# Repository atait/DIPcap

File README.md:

# DIPcap

A variable capacitor bank built from DIP switches. Six decades of coverage (1 nF to 1 mF) for under $10 to build.

[Explore the files on KiCanvas](https://kicanvas.org/?repo=https%3A%2F%2Fgithub.com%2Fatait%2FDIPcap%2Ftree%2Fmain%2Fdipcap-src)

## What it is

DIPcap covers six decades with 24 switches arranged in three groups of eight, using a non-standard but deliberate value series that guarantees full range coverage with the optimal number of switches per decade.

The calibration guarantee is the interesting part: even with ±10% tolerance on individual capacitors, some combination of switches will converge on any target value.

## Specifications

| Parameter | Value |
|---|---|
| Range | 1 nF – 1,130 µF |
| Max voltage | 0-35V, or ±50V for values < 1 µF |
| Tolerance (dead reckoning) | ±10% |
| Parasitic capacitance (all off) | 28 pF (measured) |
| Output connector | BNC + screw terminal + pin header |
| Cost to build | ~$10/unit (panelized at 8) |

## Why these switch values?

The values per decade are **10, 18, 33, 56** (in units of the decade's base, e.g. ×100pF, ×1nF, etc.). This is not a standard E-series but is drawn from E12 so that common components are available.

Full coverage means every value between 10–100 (in normalized units) is reachable within ±10% by some switch combination, and the next lower decade handles the remaining gap.

The choice of four switches per decade follows from a coverage argument:

- 2³ = 8 steps per decade — not enough; the gap between steps (100÷8 = 12.5) exceeds the range of the next lower decade group (0–10)
- 2⁴ = 16 steps per decade — sufficient; four is the minimum power-of-2 count that guarantees full coverage

## Instructions

There are two ways to use DIPcap:
1. Dead reckoning — set by remainder approximation to within ±10%
2. Calibration — engage the series resistor, measure the RC time constant on a scope, and back out the exact capacitance regardless of component tolerance

The instructions are silkscreened on the back of the board.

## What's next

**DIPresi** — the same concept applied to resistance. Binary-weighted resistor bank with DIP switches, covering several decades of resistance.

## License

Hardware released under [CERN-OHL-S v2](LICENSE). Design files are the Complete Source as defined by the licence.

© 2026 Alex Tait — source location: https://github.com/atait/dipcap

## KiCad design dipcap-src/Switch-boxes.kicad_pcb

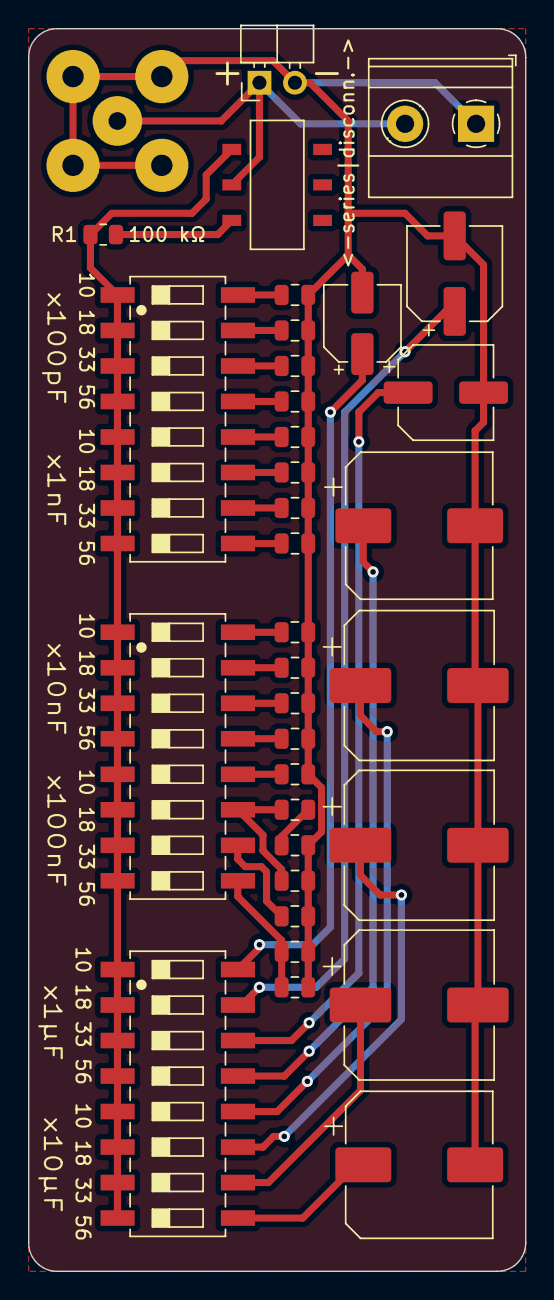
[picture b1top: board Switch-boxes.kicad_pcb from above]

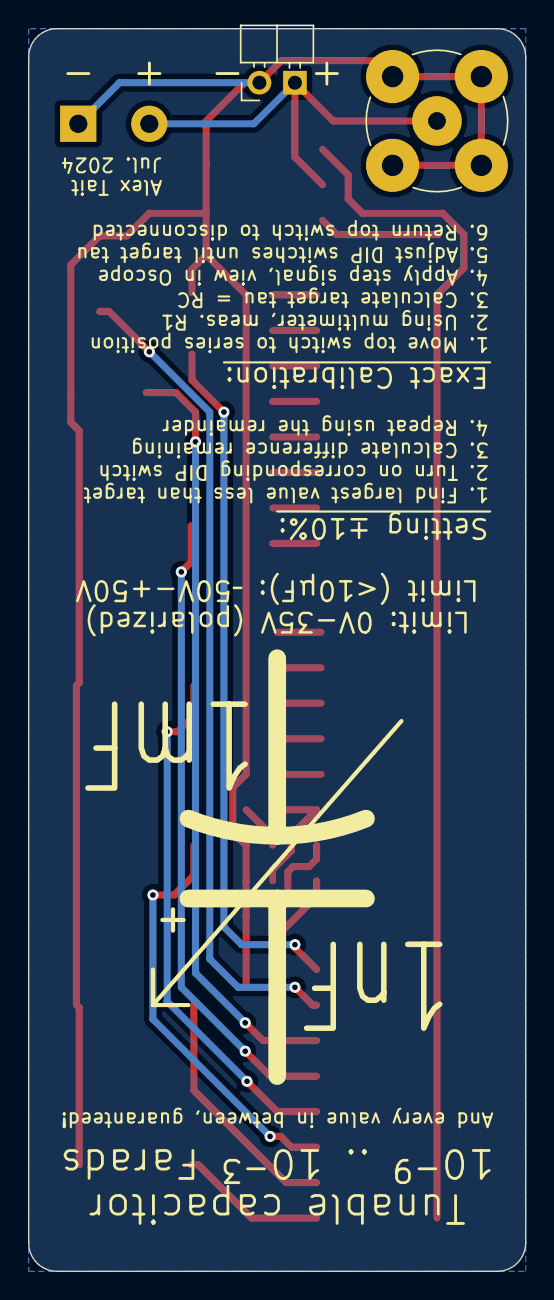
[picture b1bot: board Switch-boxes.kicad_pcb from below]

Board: 2 copper layers, 35.6 x 88.9 mm, 36 parts (2 on the bottom side), 29 nets.

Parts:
C1: 1.0 nF; C_0805_2012Metric
C2: 1.8 nF; C_0805_2012Metric
C3: 3.3 nF; C_0805_2012Metric
C4: 5.6 nF; C_0805_2012Metric
C5: 10 nF; C_0805_2012Metric
C6: 18 nF; C_0805_2012Metric
C7: 33 nF; C_0805_2012Metric
C8: 56 nF; C_0805_2012Metric
C9: 100 nF; C_0805_2012Metric
C10, C26: 180 nF; C_0805_2012Metric
C11: 330 nF; C_0805_2012Metric
C12: 560 nF; C_0805_2012Metric
C13: 1.0 uF; C_0805_2012Metric
C14, C15, C25, C27: 3.3 uF; C_0805_2012Metric
C16: 2.2 uF; C_0805_2012Metric
C17: 10 uF; CP_Elec_5x5.4
C18: 18 uF; CP_Elec_6.3x5.7
C19: 33 uF; CP_Elec_6.3x5.8
C20: 56 uF; CP_Elec_10x10
C21: 100 uF; CP_Elec_10x10.5
C22: 180 uF; CP_Elec_10x12.5
C23: 330 uF; CP_Elec_10x10.5
C24: 560 uF; CP_Elec_10x10
J1, J3: Conn_01x02; PinHeader_1x02_P2.54mm_Horizontal
J2: BNC; BNC_TEConnectivity_1478204_Vertical
J4: Conn_01x02; TerminalBlock_Phoenix_MKDS-1,5-2-5.08_1x02_P5.08mm_Horizont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
R1: 100 kΩ; R_0805_2012Metric
SW1: SW_Push_DPDT; SW_DPDT_XKB_SS-3235S-L3
SW2, SW3, SW4: SMXS-08K; SW_DIP_SPSTx08_P2.54mm_easyEDA

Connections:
unnamed: C1.1, SW2.16
unnamed: C2.1, SW2.15
unnamed: C3.1, SW2.14
unnamed: C4.1, SW2.13
unnamed: C5.1, SW2.12
unnamed: C6.1, SW2.11
unnamed: C7.1, SW2.10
unnamed: C8.1, SW2.9
unnamed: C9.1, SW3.16
unnamed: C10.1, SW3.15
unnamed: C11.1, SW3.14
unnamed: C12.1, SW3.13
unnamed: C13.1, SW3.12
unnamed: C14.1, C25.2
unnamed: C15.1, SW3.10
unnamed: C16.1, C27.1, SW3.9
unnamed: C17.1, SW4.16
unnamed: C18.1, SW4.15
unnamed: C19.1, SW4.14
unnamed: C20.1, SW4.13
unnamed: C21.1, SW4.12
unnamed: C22.1, SW4.11
unnamed: C23.1, SW4.10
unnamed: C24.1, SW4.9
unnamed: C25.1, C26.1, SW3.11
unnamed: J1.1, J2.1 (In), J4.2, SW1.2 (B)
unnamed: C1.2, C2.2, C3.2, C4.2, C5.2, C6.2, C7.2, C8.2, C9.2, C10.2, C11.2, C12.2, C13.2, C14.2, C15.2, C16.2, C17.2, C18.2, C19.2, C20.2, C21.2, C22.2, C23.2, C24.2, C26.2, C27.2, J1.2, J2.2 (Ext), J4.1
unnamed: R1.1, SW1.3 (C), SW2.1, SW2.2, SW2.3, SW2.4, SW2.5, SW2.6, SW2.7, SW2.8, SW3.1, SW3.2, SW3.3, SW3.4, SW3.5, SW3.6, SW3.7, SW3.8, SW4.1, SW4.2, SW4.3, SW4.4, SW4.5, SW4.6, SW4.7, SW4.8
unnamed: R1.2, SW1.1 (A)

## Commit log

2026-06-05 added license
2026-06-06 source files
2026-06-06 Read me
2026-06-06 updated tolerance numbers
2026-06-06 kicanvas link
2026-06-06 changed path to make room for future spin offs
